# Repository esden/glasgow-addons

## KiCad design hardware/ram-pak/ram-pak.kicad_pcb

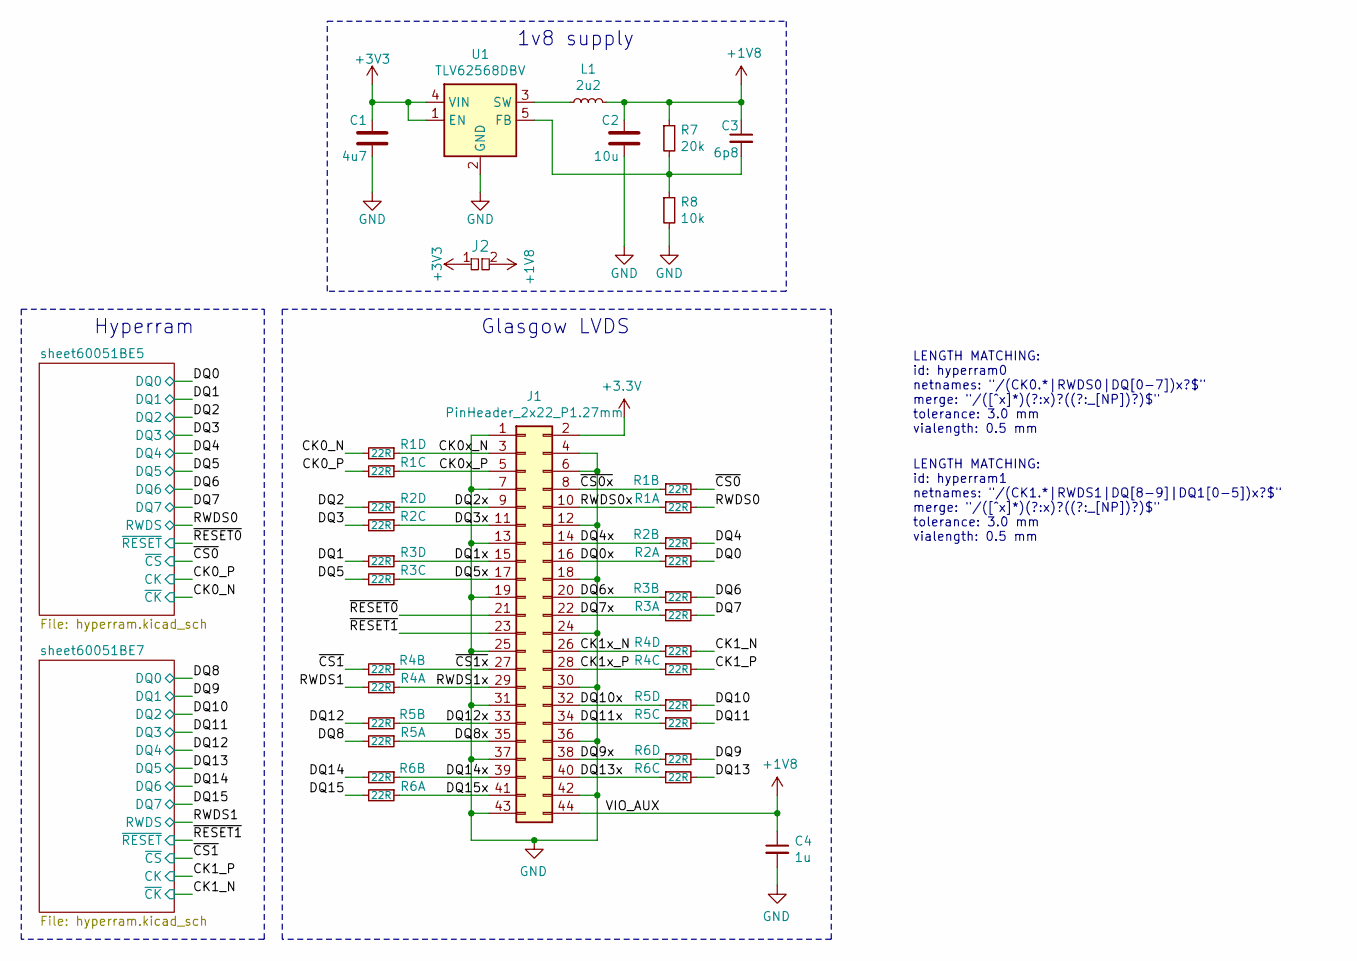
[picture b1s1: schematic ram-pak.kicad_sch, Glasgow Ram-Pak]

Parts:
C1: 4u7; C_0603
C2: 10u; C_0603
C3: 6p8; C_0402
C4: 1u; C_0402
J1: PinHeader_2x22_P1.27mm; PinSocket_2x22_P1.27mm_Vertical_Pass-Through__SMD; MPN FTS-122-01-L-DV
J2: pkl_jumper; J_0603
L1: 2u2; L_0805
R1, R2, R3, R4, R5, R6: 22R; R_Array_Convex_4x0402
R7: 20k; R_0402
R8: 10k; R_0402
U1: TLV62568DBV; SOT-23-5

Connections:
+1V8: C2.1, C3.1, C4.1, J1.44, J2.2, L1.1, R7.1; also elsewhere on the board
/CK0_N: R1.8; also elsewhere on the board
/CK0_P: R1.6; also elsewhere on the board
/CK0x_N: J1.3, R1.7
/CK0x_P: J1.5, R1.5
/CK1_N: R4.8; also elsewhere on the board
/CK1_P: R4.6; also elsewhere on the board
/CK1x_N: J1.26, R4.7
/CK1x_P: J1.28, R4.5
/DQ0: R2.2; also elsewhere on the board
/DQ0x: J1.16, R2.1
/DQ1: R3.8; also elsewhere on the board
/DQ1x: J1.15, R3.7
/DQ2: R2.8; also elsewhere on the board
/DQ2x: J1.9, R2.7
/DQ3: R2.6; also elsewhere on the board
/DQ3x: J1.11, R2.5
/DQ4: R2.4; also elsewhere on the board
/DQ4x: J1.14, R2.3
/DQ5: R3.6; also elsewhere on the board
/DQ5x: J1.17, R3.5
/DQ6: R3.4; also elsewhere on the board
/DQ6x: J1.20, R3.3
/DQ7: R3.2; also elsewhere on the board
/DQ7x: J1.22, R3.1
/DQ8: R5.2; also elsewhere on the board
/DQ8x: J1.35, R5.1
/DQ9: R6.8; also elsewhere on the board
/DQ9x: J1.38, R6.7
/DQ10: R5.8; also elsewhere on the board
/DQ10x: J1.32, R5.7
/DQ11: R5.6; also elsewhere on the board
/DQ11x: J1.34, R5.5
/DQ12: R5.4; also elsewhere on the board
/DQ12x: J1.33, R5.3
/DQ13: R6.6; also elsewhere on the board
/DQ13x: J1.40, R6.5
/DQ14: R6.4; also elsewhere on the board
/DQ14x: J1.39, R6.3
/DQ15: R6.2; also elsewhere on the board
/DQ15x: J1.41, R6.1
/RWDS0: R1.2; also elsewhere on the board
/RWDS0x: J1.10, R1.1
/RWDS1: R4.2; also elsewhere on the board
/RWDS1x: J1.29, R4.1
/~CS0x: J1.8, R1.3
/~CS0: R1.4; also elsewhere on the board
/~CS1x: J1.27, R4.3
/~CS1: R4.4; also elsewhere on the board
/~RESET0: J1.21; also elsewhere on the board
/~RESET1: J1.23; also elsewhere on the board
GND: C1.2, C2.2, C4.2, J1.1, J1.4, J1.6, J1.7, J1.12, J1.13, J1.18, J1.19, J1.24, J1.25, J1.30, J1.31, J1.36, J1.37, J1.42, J1.43, R8.2, U1.2 (GND); also elsewhere on the board
unnamed: C3.2, R7.2, R8.1, U1.5 (FB)
unnamed: L1.2, U1.3 (SW)

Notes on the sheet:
LENGTH MATCHING: id: hyperram0 netnames: "/(CK0.*|RWDS0|DQ[0-7])x?$" merge: "/([^x]*)(?:x)?((?:_[NP])?)$" tolerance: 3.0 mm vialength: 0.5 mm
Glasgow LVDS
LENGTH MATCHING: id: hyperram1 netnames: "/(CK1.*|RWDS1|DQ[8-9]|DQ1[0-5])x?$" merge: "/([^x]*)(?:x)?((?:_[NP])?)$" tolerance: 3.0 mm vialength: 0.5 mm
1v8 supply
Hyperram

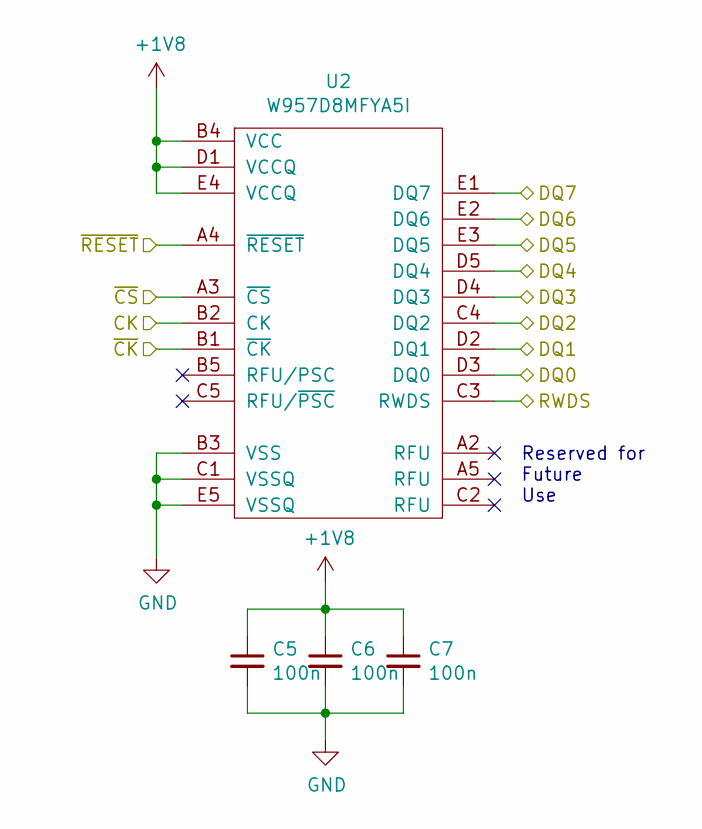
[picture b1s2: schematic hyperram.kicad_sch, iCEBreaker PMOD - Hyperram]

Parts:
C5, C6, C7: 100n; C_0402
U2: W957D8MFYA5I; BGA-24_5x5_6.0x8.0mm

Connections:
+1V8: C5.1, C6.1, C7.1, U2.B4 (VCC), U2.D1 (VCCQ), U2.E4 (VCCQ); also elsewhere on the board
/CK0_N: U2.B1 (~CK); also elsewhere on the board
/CK0_P: U2.B2 (CK); also elsewhere on the board
/DQ0: U2.D3 (DQ0); also elsewhere on the board
/DQ1: U2.D2 (DQ1); also elsewhere on the board
/DQ2: U2.C4 (DQ2); also elsewhere on the board
/DQ3: U2.D4 (DQ3); also elsewhere on the board
/DQ4: U2.D5 (DQ4); also elsewhere on the board
/DQ5: U2.E3 (DQ5); also elsewhere on the board
/DQ6: U2.E2 (DQ6); also elsewhere on the board
/DQ7: U2.E1 (DQ7); also elsewhere on the board
/RWDS0: U2.C3 (RWDS); also elsewhere on the board
/~CS0: U2.A3 (~CS); also elsewhere on the board
/~RESET0: U2.A4 (~RESET); also elsewhere on the board
GND: C5.2, C6.2, C7.2, U2.B3 (VSS), U2.C1 (VSSQ), U2.E5 (VSSQ); also elsewhere on the board

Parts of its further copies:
C8, C9, C10: 100n; C_0402
U3: W957D8MFYA5I; BGA-24_5x5_6.0x8.0mm

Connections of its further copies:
+1V8: C8.1, C9.1, C10.1, U3.B4 (VCC), U3.D1 (VCCQ), U3.E4 (VCCQ); also elsewhere on the board
/CK1_N: U3.B1 (~CK); also elsewhere on the board
/CK1_P: U3.B2 (CK); also elsewhere on the board
/DQ8: U3.D3 (DQ0); also elsewhere on the board
/DQ9: U3.D2 (DQ1); also elsewhere on the board
/DQ10: U3.C4 (DQ2); also elsewhere on the board
/DQ11: U3.D4 (DQ3); also elsewhere on the board
/DQ12: U3.D5 (DQ4); also elsewhere on the board
/DQ13: U3.E3 (DQ5); also elsewhere on the board
/DQ14: U3.E2 (DQ6); also elsewhere on the board
/DQ15: U3.E1 (DQ7); also elsewhere on the board
/RWDS1: U3.C3 (RWDS); also elsewhere on the board
/~CS1: U3.A3 (~CS); also elsewhere on the board
/~RESET1: U3.A4 (~RESET); also elsewhere on the board
GND: C8.2, C9.2, C10.2, U3.B3 (VSS), U3.C1 (VSSQ), U3.E5 (VSSQ); also elsewhere on the board

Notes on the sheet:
Reserved for Future Use

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
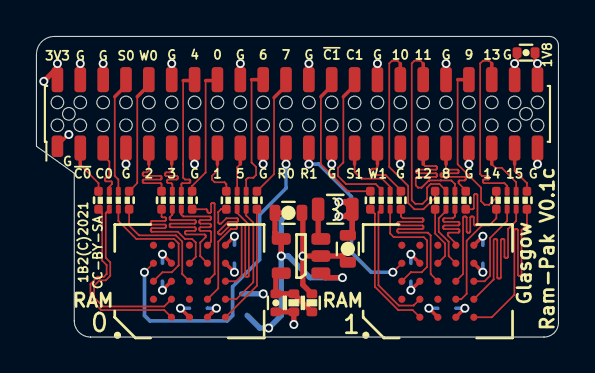
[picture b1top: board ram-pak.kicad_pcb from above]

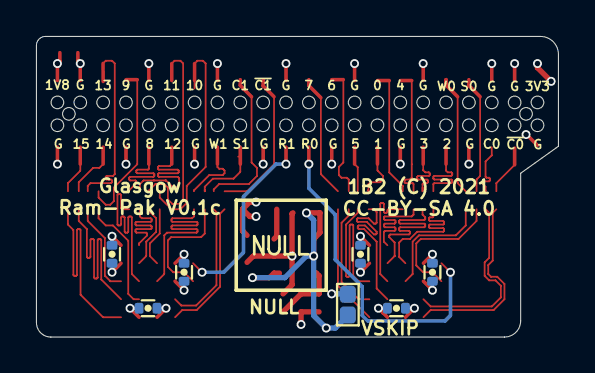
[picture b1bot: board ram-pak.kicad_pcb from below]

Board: 4 copper layers, 29.0 x 16.7 mm, 24 parts (7 on the bottom side), 55 nets.

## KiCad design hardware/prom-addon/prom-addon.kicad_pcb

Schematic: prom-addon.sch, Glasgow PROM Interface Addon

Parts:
C1, C2: 100n; C_0402
J1, J2: Conn_02x10_Odd_Even; PinSocket_2x10_P2.54mm_Vertical
JP1, JP2: Pin Mode; PinHeader_1x03_P2.54mm_Vertical
RN1, RN2, RN3: 33R; R_Array_Convex_4x0402
U1, U2: 74HC595; DHVQFN-16_2.5x3.5mm_Pitch0.5mm
U3: 27C512; DIP-28_W15.24mm

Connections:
/A0: J1.3, U3.10 (A0)
/A1: J1.5, U3.9 (A1)
/A2: J1.7, U3.8 (A2)
/A3: J1.9, U3.7 (A3)
/A4: RN1.1 (R1.1), U3.6 (A4)
/A5: RN1.2 (R2.1), U3.5 (A5)
/A6: RN1.3 (R3.1), U3.4 (A6)
/A7: RN1.4 (R4.1), U3.3 (A7)
/A8: RN2.1 (R1.1), U3.25 (A8)
/A9: RN2.2 (R2.1), U3.24 (A9)
/A10: RN2.3 (R3.1), U3.21 (A10)
/A11: RN2.4 (R4.1), U3.23 (A11)
/A12: RN3.1 (R1.1), U3.2 (A12)
/A13: RN3.2 (R2.1), U3.26 (A13)
/A14: JP1.1 (A), RN3.3 (R3.1)
/A15: JP2.1 (A), RN3.4 (R4.1)
/A_CLK: J1.11, U1.11, U2.11
/A_LATCH: J1.13, U1.12, U2.12
/A_SI: J1.15, U1.14
/A_SI´: U1.9, U2.14
/DQ0: J2.3, U3.11 (D0)
/DQ1: J2.5, U3.12 (D1)
/DQ2: J2.7, U3.13 (D2)
/DQ3: J2.9, U3.15 (D3)
/DQ4: J2.11, U3.16 (D4)
/DQ5: J2.13, U3.17 (D5)
/DQ6: J2.15, U3.18 (D6)
/DQ7: J2.17, U3.19 (D7)
/P1: JP2.2 (C), U3.1 (A15)
/P27: JP1.2 (C), U3.27 (A14)
/~OE: J1.17, U3.20 (~CE), U3.22 (~OE)
GND: C1.2, C2.2, J1.4, J1.6, J1.8, J1.10, J1.12, J1.14, J1.16, J1.18, J2.4, J2.6, J2.8, J2.10, J2.12, J2.14, J2.16, J2.18, JP2.3 (B), U1.8, U1.13, U1.17, U2.8, U2.13, U2.17, U3.14 (GND)
unnamed: RN1.5 (R4.2), U1.3
unnamed: RN1.6 (R3.2), U1.2
unnamed: RN1.7 (R2.2), U1.1
unnamed: RN1.8 (R1.2), U1.15
unnamed: RN2.5 (R4.2), U1.7
unnamed: RN2.6 (R3.2), U1.6
unnamed: RN2.7 (R2.2), U1.5
unnamed: RN2.8 (R1.2), U1.4
unnamed: RN3.5 (R4.2), U2.3
unnamed: RN3.6 (R3.2), U2.2
unnamed: RN3.7 (R2.2), U2.1
unnamed: RN3.8 (R1.2), U2.15
VCC: C1.1, C2.1, J1.1, J1.2, J2.1, J2.2, JP1.3 (B), U1.10, U1.16, U2.10, U2.16, U3.28 (VCC)

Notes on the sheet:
Can be ~PGM~ or A14
Can be Vpp or A15

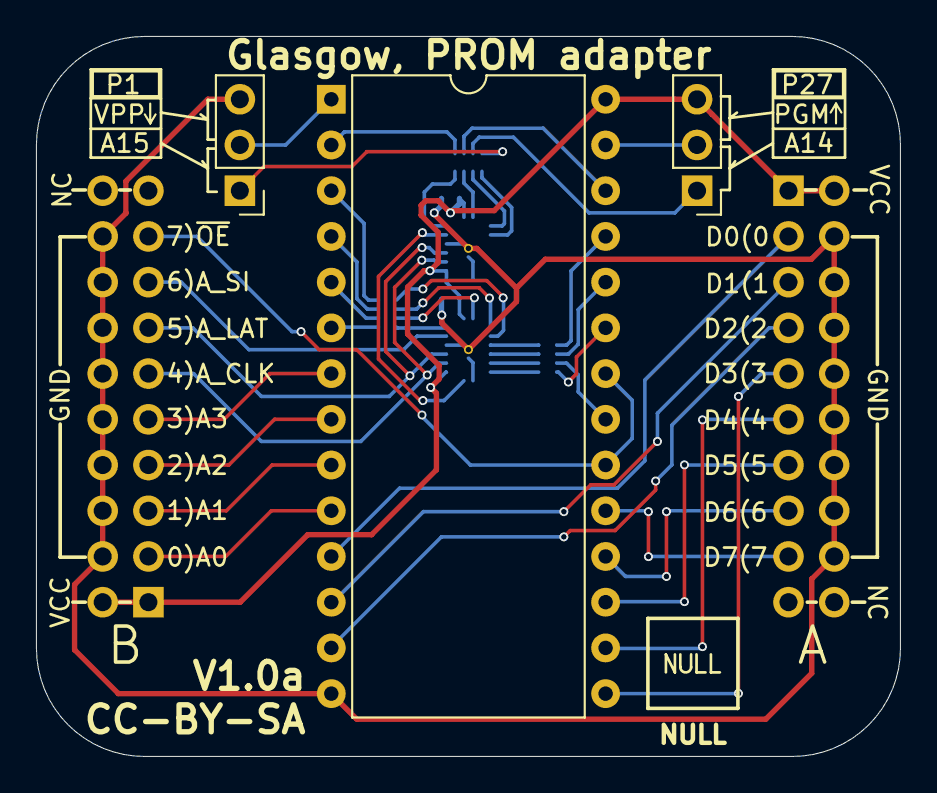
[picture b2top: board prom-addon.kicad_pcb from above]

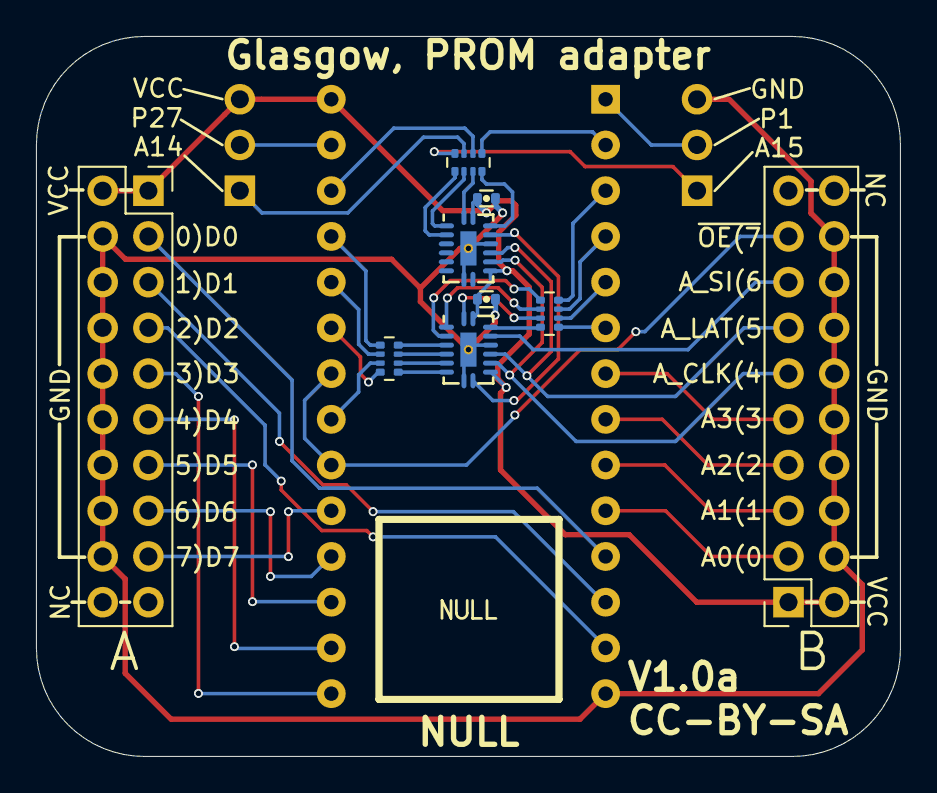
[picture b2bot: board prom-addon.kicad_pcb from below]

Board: 2 copper layers, 48.0 x 40.0 mm, 12 parts (9 on the bottom side), 45 nets.

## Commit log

2020-08-26 prom interface addon initial commit.
2020-09-03 The ROM reader addon schematic finished.
    We are pretty much ready for layout. Status as of @esden twitch stream
    on 2020-09-01.
2020-09-30 prom: Routed the first version of the board.
2020-10-14 Updated PKL.
2020-10-14 Replaced supply fills with point to point routing.
    Will look better in afterdark. ;)
2020-10-15 Silkscreen minor fixes.
2020-10-27 Added schematic pdf.
2021-01-18 prom: Added silkscreen legend. Bumped version.
2021-01-27 Initial commit of the RAM Pak for the LVDS connector.
2021-01-27 Added ram-pak schematic pdf.
2021-01-31 Added missing 3d models.
2021-02-10 Ram-Pak: Routed and length matched.
2021-02-10 Ram-Pak: Updated schematic PDF plot.
2021-02-13 ram-pak: silkscreen improvements.
2021-02-13 ram-pak: Some more silkscreen work.
2021-02-13 ram-pak: Fab layer placement plan cleanup.
2021-02-13 ram-pak: Extended and updated BOM information.
2021-02-16 ram-pak: Removed back pads, added VSKIP bumped version.
    * Removed the back side connector mounting pads. (only needed for the
    first prototype using 1.6mm thick pcb)
    * Added VSKIP that allows the use of 3v3 RAM chips.
    * Bumped version to V0.1b
2021-02-16 ram-pak: VSKIP jumper position adjusted.
2021-02-16 ram-pak: Cleaned up fab layer.
2021-07-05 ram-pak: Increased pad hole gap for improved assembly.
2021-07-05 ram-pak: Moved some of the passives and traces from the board edge.
    This should make it slightly more mechanically robust and easier to
    assemble.
2021-07-05 ram-pak: Some VREG routing cleanup.
2021-07-29 ram-pak: Increased hole trace spacing to 0.2mm.
    To reliably manufacture the ram-pak the traces need to be at least 0.2mm
    from the NPTH pin header holes. To accomplish that we had to find a
    different way to lengthmatch the traces.
    Bumped version to 0.1c.
2021-07-29 ram-pak: Slightly increased pad gap for the r-paks.
    If we can it is good to get solder mask bridges on the r-paks.
2021-07-29 ram-pak: Some silkscreen cleanup.
2023-10-24 Updated ram-pak files to KiCad V7.
2023-10-24 Added KiCad V7 gitignores.

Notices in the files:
hardware/prom-addon/prom-addon.kicad_pcb:
(C) 2020-2021 1BitSquared
(C) 2020-2021 Piotr Esden-Tempski
License: CC-BY-SA 4.0
CC-BY-SA
hardware/ram-pak/ram-pak.kicad_pcb:
(C) 2021 1BitSquared
(C) 2021 Piotr Esden-Tempski
1B2 (C) 2021
CC-BY-SA 4.0
